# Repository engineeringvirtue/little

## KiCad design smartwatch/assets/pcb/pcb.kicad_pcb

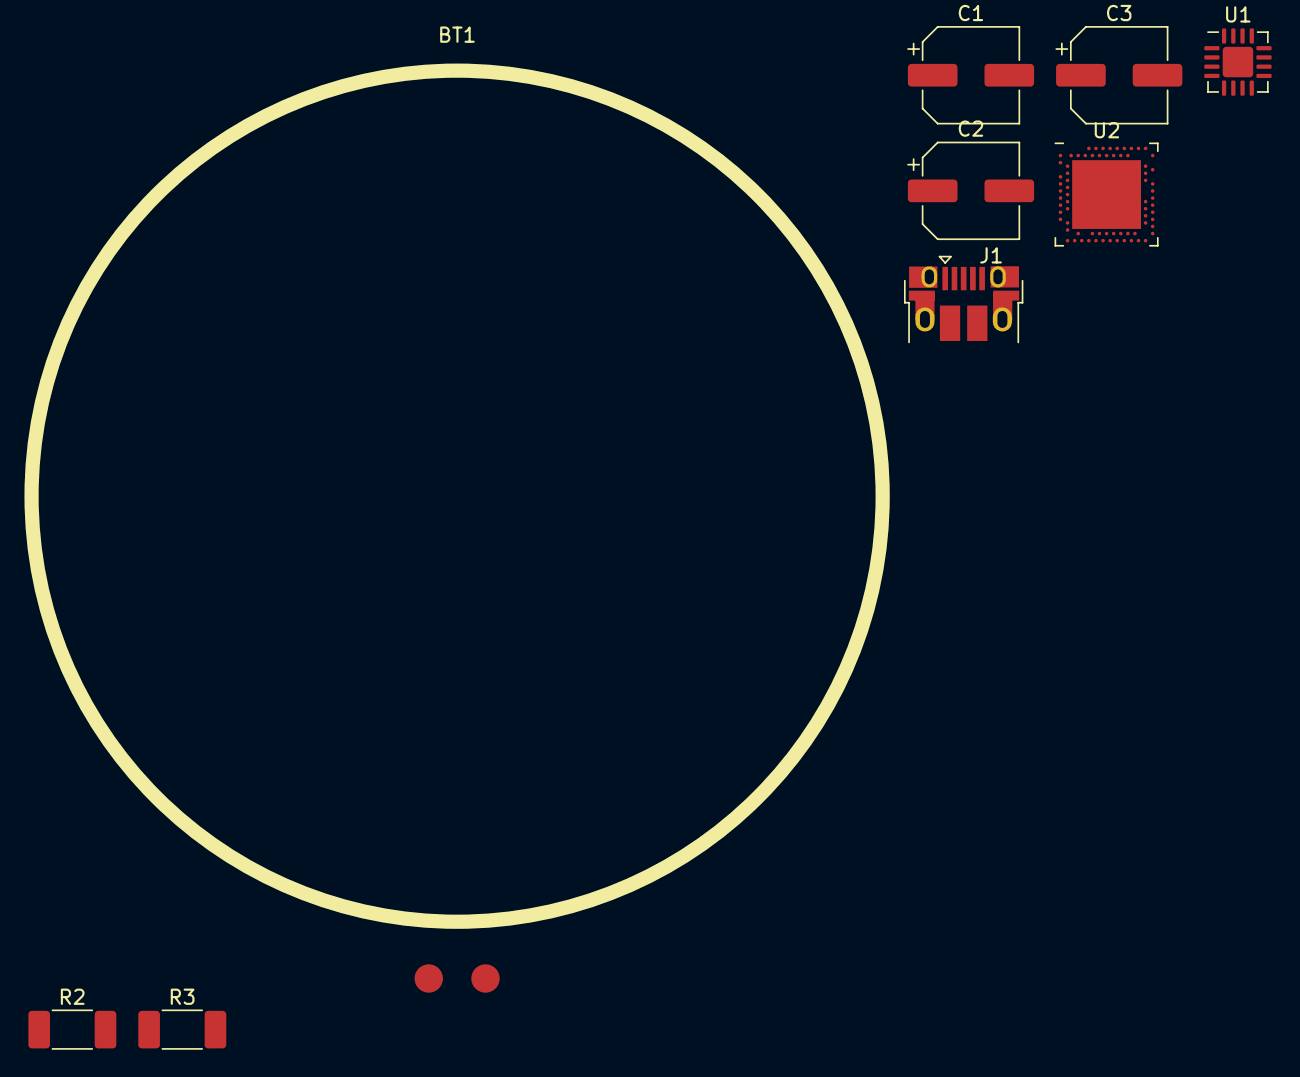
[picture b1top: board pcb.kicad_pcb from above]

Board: 2 copper layers, 9 parts (0 on the bottom side), 9 nets, no tracks yet.

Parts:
BT1: Battery_Cell; Battery_Illinois_Capacitor_RJD3048ST1
C1, C2: 10uf; CP_Elec_6.3x5.4_Nichicon
C3: 31.25uF; CP_Elec_6.3x5.4_Nichicon
J1: USB_B_Micro; USB_Micro-B_Amphenol_10103594-0001LF_Horizontal
R2: 52.3k; R_2010_5025Metric_Pad1.52x2.65mm_HandSolder
R3: 100K; R_2010_5025Metric_Pad1.52x2.65mm_HandSolder
U1: LTC4055; QFN-16-1EP_4x4mm_P0.65mm_EP2.15x2.15mm
U2: nRF52840; Nordic_AQFN-73-1EP_7x7mm_P0.5mm

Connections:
/CHRG: U1.14, U2.A12
/D+: J1.3, U2.AD6
/D-: J1.2, U2.AD4
GND: BT1.1, C1.1, C2.1, C3.1, J1.5, R2.2, R3.2, U1.10, U1.16, U1.17, U2.B7, U2.EP, U2.F23
unnamed: C1.2, J1.1, U1.1, U1.4
unnamed: C3.2, U1.12
unnamed: R2.1, U1.9
unnamed: R3.1, U2.A22, U2.AD14, U2.AD23, U2.B1, U2.W1
VCC: C2.2, U1.3, U2.Y2

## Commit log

2019-05-11 init
2019-05-13 opengLL
2019-05-13 yaye
2019-05-13 aaaaaaaaaaaaaaa
2019-05-13 image rendering works now
2019-05-14 it works again
2019-05-15 triangles & more
2019-05-15 dynamic triangles
2019-05-16 font rendering - only for A
2019-05-16 smol fiexs
2019-05-16 cargo workspaces exist + font fixed
2019-05-16 fonts
2019-05-17 Renamed Pos to Vector2
2019-05-17 hecc
2019-05-17 antialiasing
2019-05-18 triengles
2019-05-18 insanity
2019-05-18 circle attempt and fail
2019-05-18 animations!
2019-05-18 easing functions
2019-05-18 Updated ease.rs
2019-05-18 Updated ease.rs (again) :/
2019-05-18 lol pub mod ease;
2019-05-19 animations
2019-05-20 adfgadgadfg
2019-05-21 draweee
2019-05-21 spaces to tabs...
2019-05-22 TRI ANGL ES
2019-05-22 trANsFormATion
2019-05-23 Matrix
2019-05-23 Cool thing
2019-05-23 raylob
2019-05-23 matrixsh
2019-05-23 Circles and Arcsssss
2019-05-23 Fixed indents
2019-05-24 We got ellipse
2019-05-24 123467890
2019-05-24 ELLIPSEIS E SIHAHHHSH
2019-05-25 Matrix is dead
2019-05-25 Fixed weird stuff because Rust is weird
2019-05-25 Indent fixed
2019-05-25 Me aweseome
2019-05-25 Me smart
2019-05-25 A start
2019-05-26 qt project
2019-05-29 bork
2019-05-29 oopos fuck
2019-06-03 Improved ellipse/circle algo
2019-06-03 aaaaaaaaaaaa
2019-07-09 CIRCLES!!!!!1111
2019-07-09 ROTATION!!!!!!!!!!!!!!!!!!!!!!!!!!!!!!
2019-07-12 pcb, qemu & more!
